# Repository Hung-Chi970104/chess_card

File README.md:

# Pico Chess Card
Ever think of playing chess on the size of a business card? Welcome to the Pico Chess Card!

After building my Tic-Tac-Toe business card, I decided to build a more advanced version that allows users to play chess, compete online through radio, and even compete against AI!

https://github.com/user-attachments/assets/676e2b21-aca0-44f8-8b26-b48a64608b89

# Features
- Pass-and-play mode (like one device but two people take turn)
- Online 1v1 through nrf24l01 (*Will be added in V2!)
- NFC tap to either go to websites or pairing mode

# Components
- RP2040
- 12MHz Crystal (ABM8-272-T3)
- 8MB Flash Storage (W25Q64JVXGIQ)
- Buck-Boost Switching Regulator (RT6150B)
- USB-C (TYPE-C-31-M-12)

# PCB Designs
- 2 layers
- Single-sided component placement
- 2.6mm board thickness
- HASL (with lead) surface finish
- 1oz outer copper weight

## PCB Schematic

## PCB Layouts

## 3D Model

# How to order
- Download the zip file
- Upload the zip file to JLCPCB
- Select PCBA and continue
- Upload BOM.csv and position.csv
- Select the parts and submit payment

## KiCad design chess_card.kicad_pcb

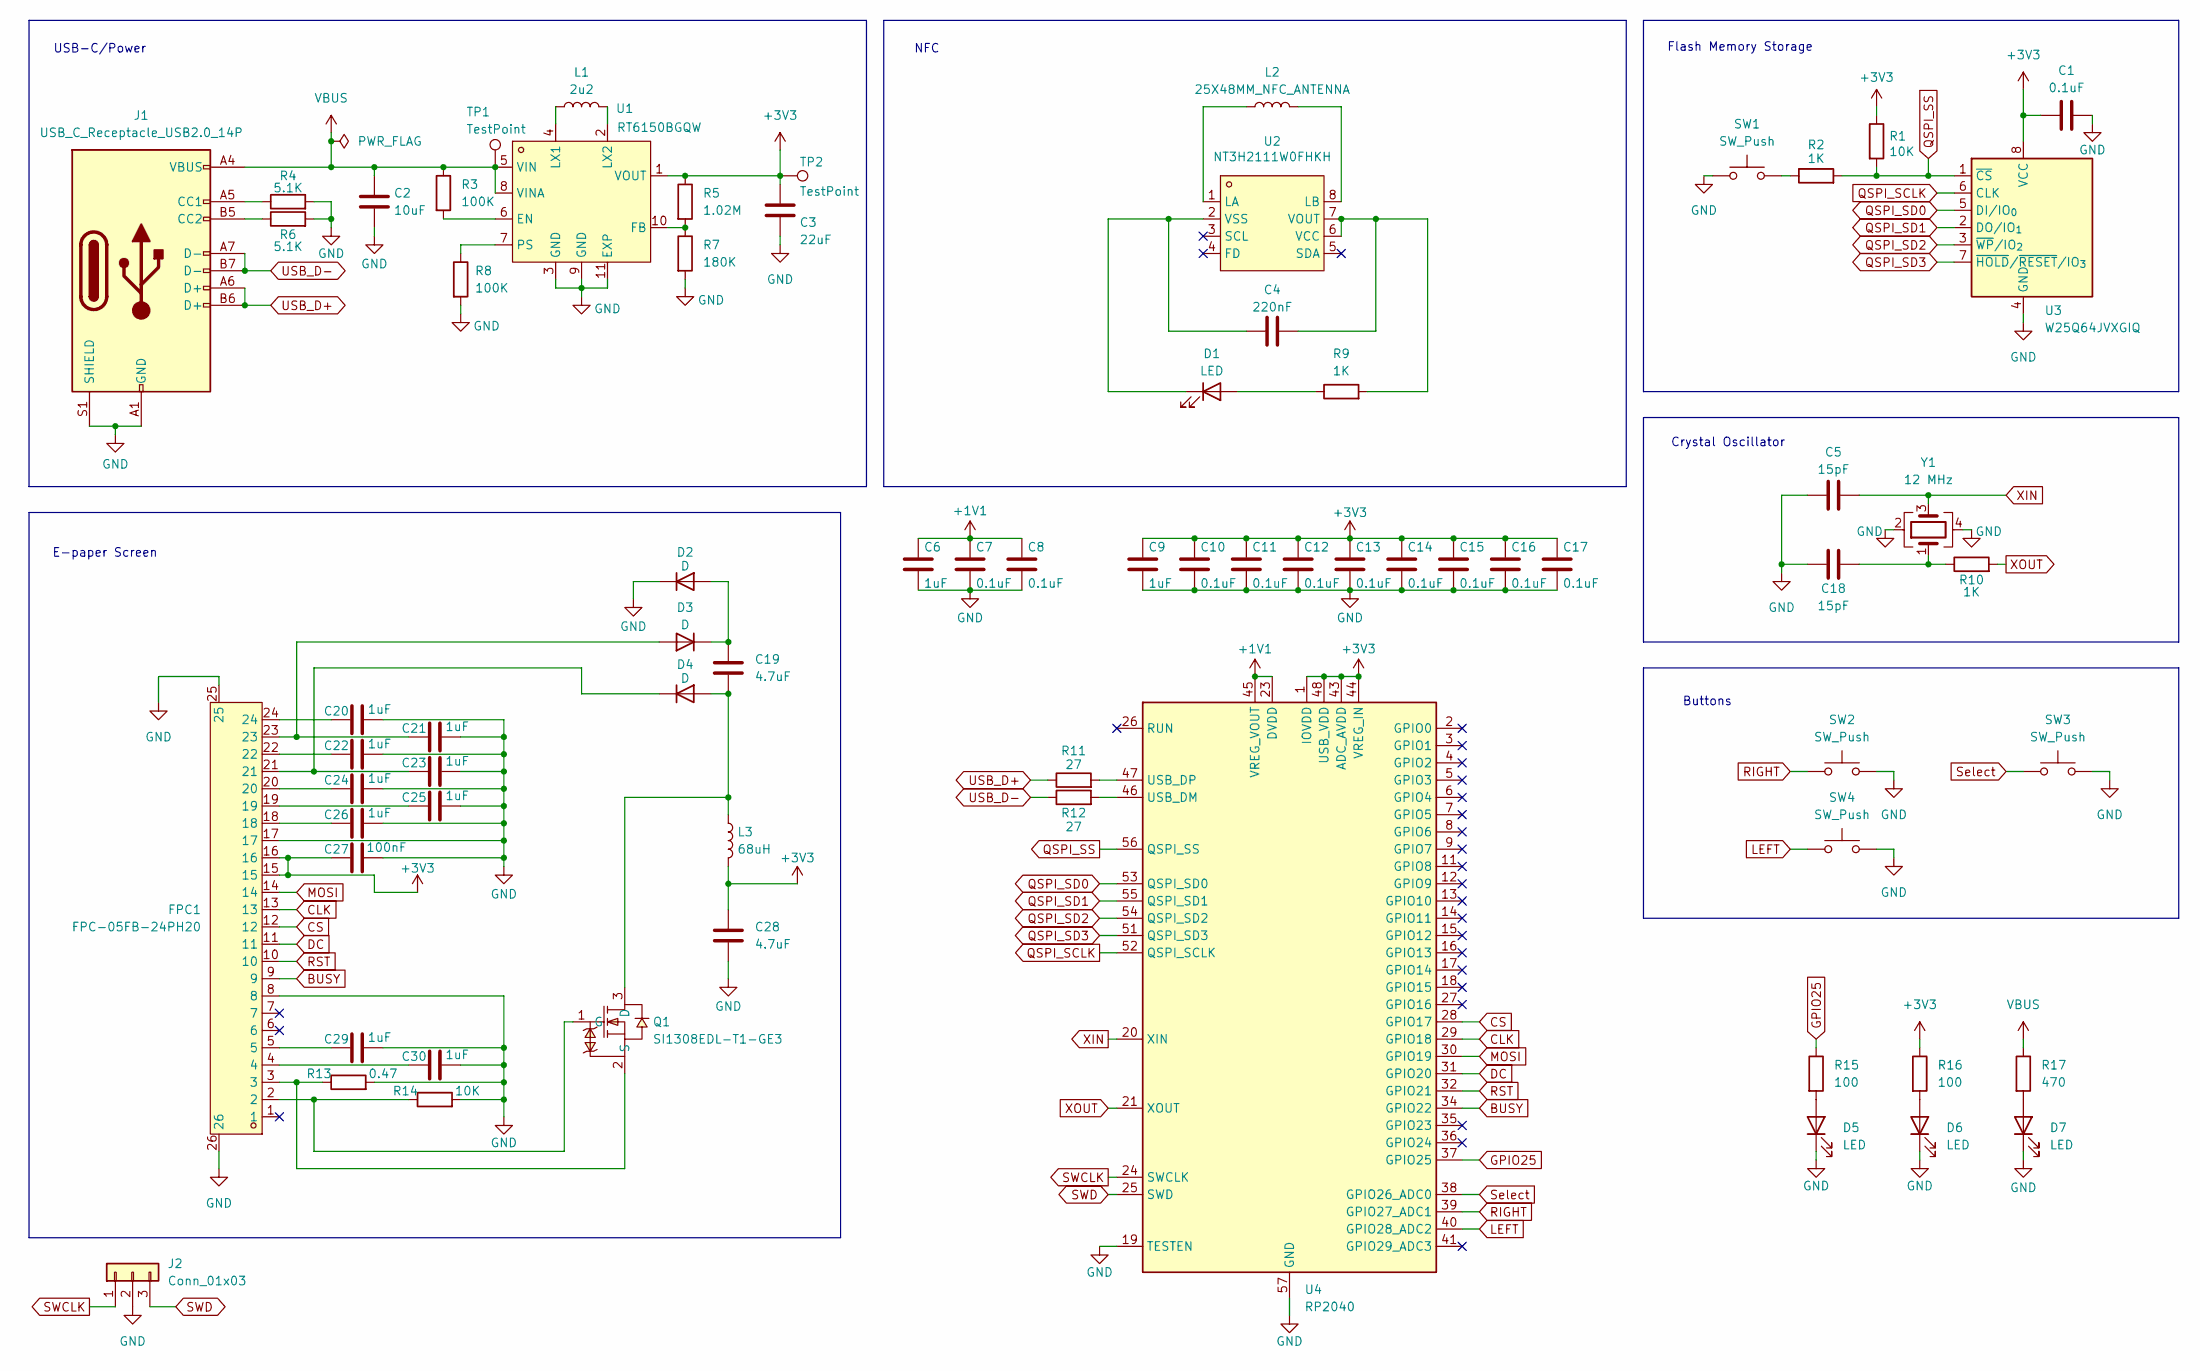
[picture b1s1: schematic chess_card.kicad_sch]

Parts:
C1, C7, C8, C10, C11, C12, C13, C14, C15, C16, C17: 0.1uF; C_0402_1005Metric
C2: 10uF; C_1206_3216Metric
C3: 22uF; C_1206_3216Metric
C4: 220nF; C_0603_1608Metric
C5, C18: 15pF; C_0402_1005Metric
C6, C9: 1uF; C_0402_1005Metric
C19, C28: 4.7uF; C_0603_1608Metric
C20, C21, C22, C23, C24, C25, C26, C29, C30: 1uF; C_0603_1608Metric
C27: 100nF; C_0603_1608Metric
D1: LED; LED_0402_1005Metric
D2, D3, D4: D; D_SOD-323
D5, D6, D7: LED; LED_0805_2012Metric
FPC1: FPC-05FB-24PH20; FPC-SMD_24P-P0.50_FPC-05FB-24PH20; LCSC Part C2856831
J1: USB_C_Receptacle_USB2.0_14P; USB_C_Receptacle_HRO_TYPE-C-31-M-12
J2: Conn_01x03; PinHeader_1x03_P2.54mm_Vertical
L1: 2u2; L_1008_2520Metric
L2: 25X48MM_NFC_ANTENNA
L3: 68uH; L_0805_2012Metric
Q1: SI1308EDL-T1-GE3; SOT-323_L2.0-W1.3-P1.30-LS2.1-BR; LCSC Part C469327
R1: 10K; R_0402_1005Metric
R2, R10: 1K; R_0402_1005Metric
R3, R8: 100K; R_0402_1005Metric
R4, R6: 5.1K; R_0402_1005Metric
R5: 1.02M; R_0402_1005Metric
R7: 180K; R_0402_1005Metric
R9: 1K; R_0402_1005Metric; LCSC C23182
R11, R12: 27; R_0402_1005Metric
R13: 0.47; R_0603_1608Metric
R14: 10K; R_0603_1608Metric
R15, R16: 100; R_0402_1005Metric
R17: 470; R_0402_1005Metric
SW1: SW_Push; SW_Push_SPST_NO_Alps_SKRK
SW2, SW3, SW4: SW_Push; SW_SPST_SKQG_WithoutStem
TP1, TP2: TestPoint; TestPoint_Pad_1.0x1.0mm
U1: RT6150BGQW; WSON-10_L2.5-W2.5-P0.50-BL-EP; LCSC Part C147972
U2: NT3H2111W0FHKH; XQFN-8_L1.6-W1.6-P0.50-BL_NT3H2111W0FHKH; LCSC C710403
U3: W25Q64JVXGIQ; XSON-8_L4.0-W4.0-P0.80-TL-EP
U4: RP2040; QFN-56-1EP_7x7mm_P0.4mm_EP3.2x3.2mm
Y1: 12 MHz; Crystal_SMD_3225-4Pin_3.2x2.5mm

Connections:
+1V1: C6.1, C7.1, C8.1, U4.23 (DVDD), U4.45 (VREG_VOUT), U4.50 (DVDD)
+3V3: C1.1, C3.1, C9.1, C10.1, C11.1, C12.1, C13.1, C14.1, C15.1, C16.1, C17.1, C27.2, C28.1, FPC1.15, FPC1.16, L3.2, R1.1, R5.1, R16.1, TP2.1, U1.1 (VOUT), U3.8 (VCC), U4.1 (IOVDD), U4.10 (IOVDD), U4.22 (IOVDD), U4.33 (IOVDD), U4.42 (IOVDD), U4.43 (ADC_AVDD), U4.44 (VREG_IN), U4.48 (USB_VDD), U4.49 (IOVDD)
BUSY: FPC1.9, U4.34 (GPIO22)
CLK: FPC1.13, U4.29 (GPIO18)
CS: FPC1.12, U4.28 (GPIO17)
DC: FPC1.11, U4.31 (GPIO20)
GND: C1.2, C2.2, C3.2, C5.1, C6.2, C7.2, C8.2, C9.2, C10.2, C11.2, C12.2, C13.2, C14.2, C15.2, C16.2, C17.2, C18.1, C20.1, C21.1, C22.1, C23.1, C24.1, C25.1, C26.1, C27.1, C28.2, C29.1, C30.1, D2.1 (K), D5.1 (K), D6.1 (K), D7.1 (K), FPC1.8, FPC1.17, FPC1.25, FPC1.26, J1.A1 (GND), J1.A12 (GND), J1.B1 (GND), J1.B12 (GND), J1.S1 (SHIELD), J2.2, R4.2, R6.2, R7.2, R8.2, R13.2, R14.2, SW1.1, SW2.2, SW3.2, SW4.2, U1.3 (GND), U1.9 (GND), U1.11 (EXP), U3.4 (GND), U4.19 (TESTEN), U4.57 (GND), Y1.2, Y1.4
GPIO25: R15.1, U4.37 (GPIO25)
LEFT: SW4.1, U4.40 (GPIO28_ADC2)
MOSI: FPC1.14, U4.30 (GPIO19)
unnamed: C18.2, R10.1, Y1.1
unnamed: C20.2, FPC1.24
unnamed: C22.2, FPC1.22
unnamed: C24.2, FPC1.20
unnamed: C25.2, FPC1.19
unnamed: C26.2, FPC1.18
unnamed: C29.2, FPC1.5
unnamed: C30.2, FPC1.4
unnamed: D1.2 (A), R9.1
unnamed: C4.1, D1.1 (K), U2.2 (VSS)
unnamed: C19.1, D2.2 (A), D3.1 (K)
unnamed: C21.2, D3.2 (A), FPC1.23
unnamed: C19.2, D4.2 (A), L3.1, Q1.3 (D)
unnamed: C23.2, D4.1 (K), FPC1.21
unnamed: D5.2 (A), R15.2
unnamed: D6.2 (A), R16.2
unnamed: D7.2 (A), R17.2
unnamed: J1.A5 (CC1), R4.1
unnamed: J1.B5 (CC2), R6.1
unnamed: FPC1.2, Q1.1 (G), R14.1
unnamed: FPC1.3, Q1.2 (S), R13.1
unnamed: R2.1, SW1.2
unnamed: R3.2, U1.6 (EN)
unnamed: R5.2, R7.1, U1.10 (FB)
unnamed: L1.1, U1.4 (LX1)
unnamed: L1.2, U1.2 (LX2)
unnamed: R8.1, U1.7 (PS)
unnamed: L2.1, U2.1 (LA)
unnamed: L2.2, U2.8 (LB)
unnamed: C4.2, R9.2, U2.6 (VCC), U2.7 (VOUT)
unnamed: R12.2, U4.46 (USB_DM)
unnamed: R11.2, U4.47 (USB_DP)
QSPI_SCLK: U3.6 (CLK), U4.52 (QSPI_SCLK)
QSPI_SD0: U3.5 (DI/IO_{0}), U4.53 (QSPI_SD0)
QSPI_SD1: U3.2 (DO/IO_{1}), U4.55 (QSPI_SD1)
QSPI_SD2: U3.3 (~WP/IO_{2}), U4.54 (QSPI_SD2)
QSPI_SD3: U3.7 (~HOLD/~RESET/IO_{3}), U4.51 (QSPI_SD3)
QSPI_SS: R1.2, R2.2, U3.1 (~CS), U4.56 (QSPI_SS)
RIGHT: SW2.1, U4.39 (GPIO27_ADC1)
RST: FPC1.10, U4.32 (GPIO21)
SWCLK: J2.1, U4.24 (SWCLK)
SWD: J2.3, U4.25 (SWD)
Select: SW3.1, U4.38 (GPIO26_ADC0)
USB_D+: J1.A6 (D+), J1.B6 (D+), R11.1
USB_D-: J1.A7 (D-), J1.B7 (D-), R12.1
VBUS: C2.1, J1.A4 (VBUS), J1.A9 (VBUS), J1.B4 (VBUS), J1.B9 (VBUS), R3.1, R17.1, TP1.1, U1.5 (VIN), U1.8 (VINA)
XIN: C5.2, U4.20 (XIN), Y1.3
XOUT: R10.2, U4.21 (XOUT)

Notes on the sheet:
E-paper Screen
Crystal Oscillator
Flash Memory Storage
Buttons
NFC
USB-C/Power

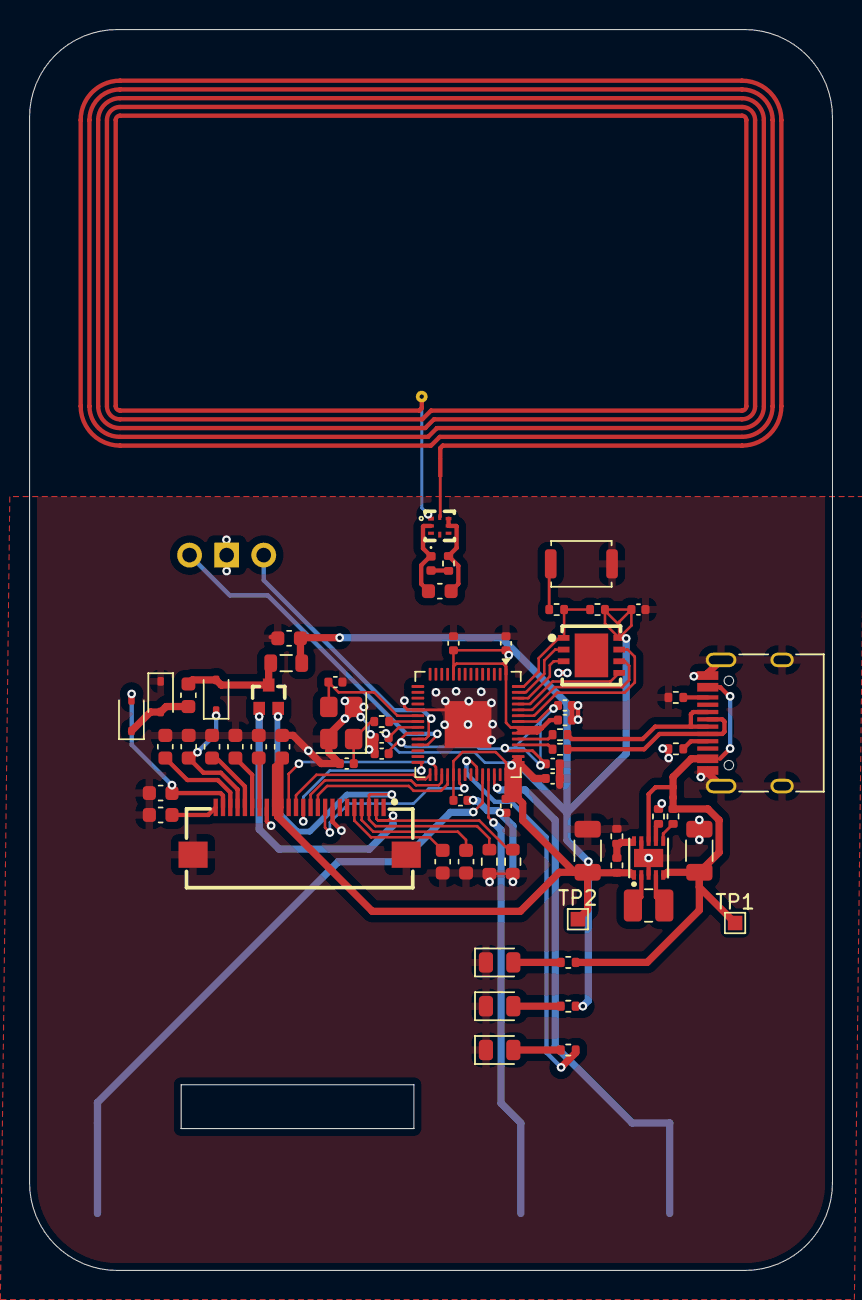
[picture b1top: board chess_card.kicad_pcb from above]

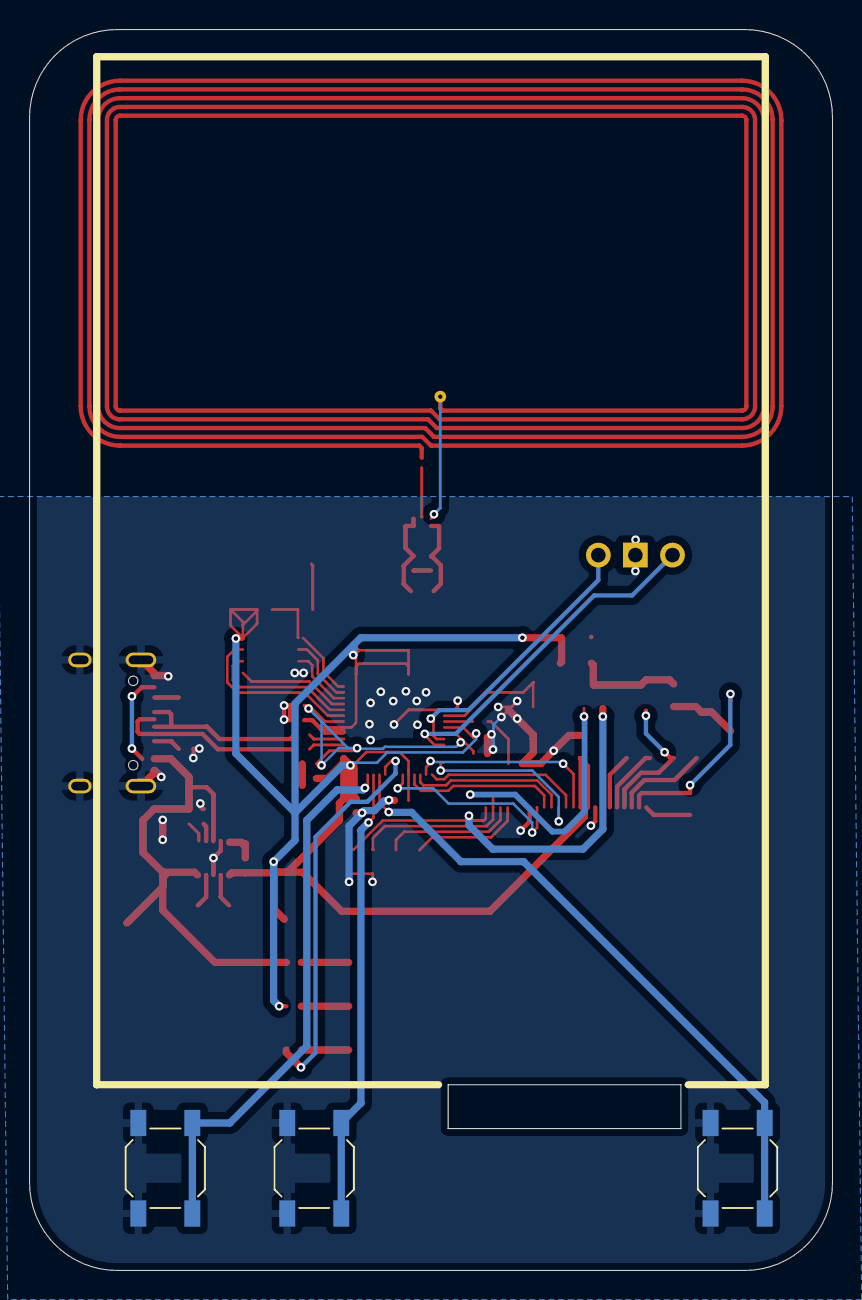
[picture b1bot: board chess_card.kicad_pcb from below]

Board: 2 copper layers, 55.0 x 85.0 mm, 70 parts (3 on the bottom side), 58 nets.

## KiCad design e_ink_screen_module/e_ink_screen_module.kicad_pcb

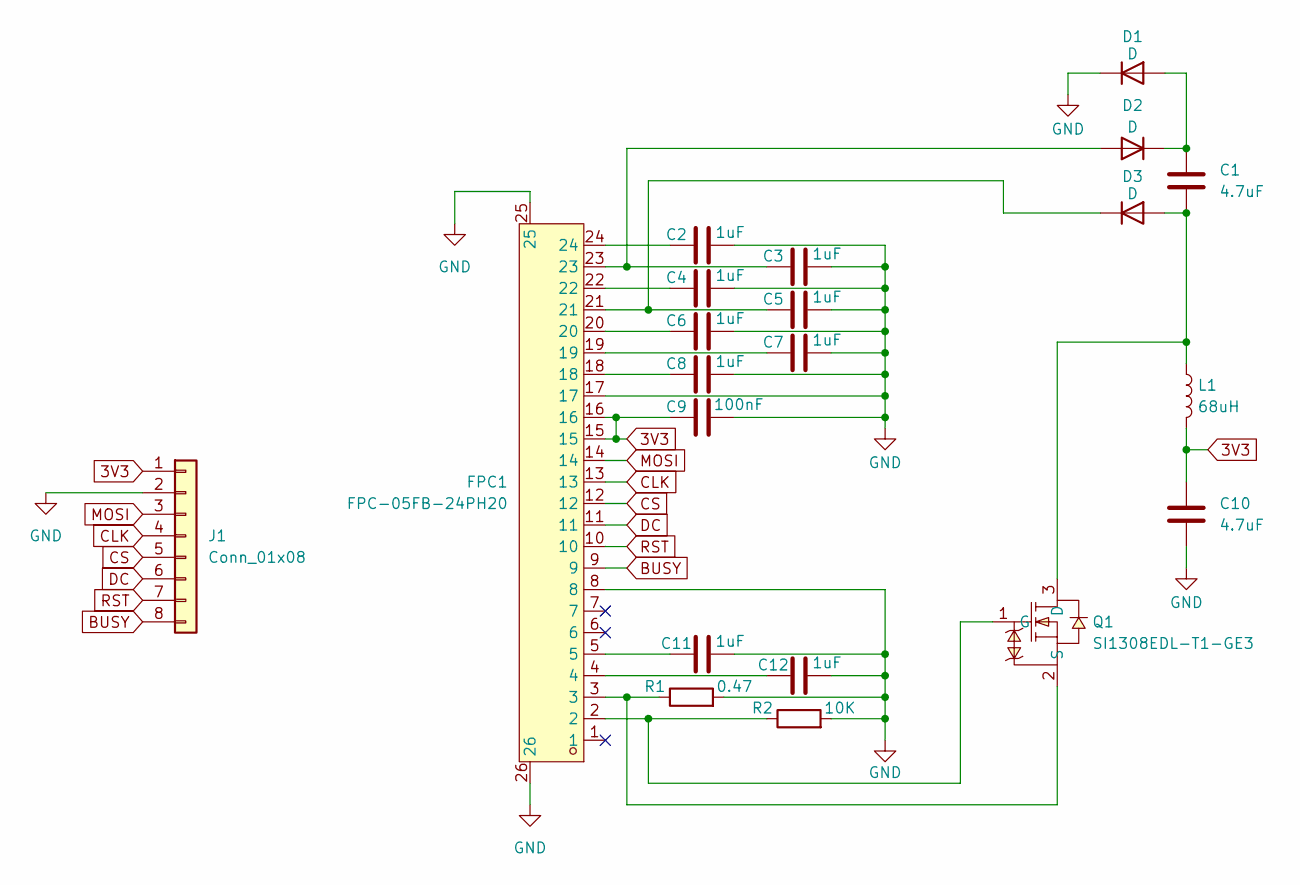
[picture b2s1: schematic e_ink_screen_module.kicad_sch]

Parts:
C1, C10: 4.7uF; C_0603_1608Metric
C2, C3, C4, C5, C6, C7, C8, C11, C12: 1uF; C_0603_1608Metric
C9: 100nF; C_0603_1608Metric
D1, D2, D3: D; D_SOD-323
FPC1: FPC-05FB-24PH20; FPC-SMD_24P-P0.50_FPC-05FB-24PH20; LCSC Part C2856831
J1: Conn_01x08; PinHeader_1x08_P2.54mm_Vertical
L1: 68uH; L_0805_2012Metric
Q1: SI1308EDL-T1-GE3; SOT-323_L2.0-W1.3-P1.30-LS2.1-BR; LCSC Part C469327
R1: 0.47; R_0603_1608Metric
R2: 10K; R_0603_1608Metric

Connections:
3V3: C9.2, C10.1, FPC1.15, FPC1.16, J1.1, L1.2
BUSY: FPC1.9, J1.8
CLK: FPC1.13, J1.4
CS: FPC1.12, J1.5
DC: FPC1.11, J1.6
GND: C2.1, C3.1, C4.1, C5.1, C6.1, C7.1, C8.1, C9.1, C10.2, C11.1, C12.1, D1.1 (K), FPC1.8, FPC1.17, FPC1.25, FPC1.26, J1.2, R1.2, R2.2
MOSI: FPC1.14, J1.3
unnamed: C2.2, FPC1.24
unnamed: C4.2, FPC1.22
unnamed: C6.2, FPC1.20
unnamed: C7.2, FPC1.19
unnamed: C8.2, FPC1.18
unnamed: C11.2, FPC1.5
unnamed: C12.2, FPC1.4
unnamed: C1.1, D1.2 (A), D2.1 (K)
unnamed: C3.2, D2.2 (A), FPC1.23
unnamed: C1.2, D3.2 (A), L1.1, Q1.3 (D)
unnamed: C5.2, D3.1 (K), FPC1.21
unnamed: FPC1.2, Q1.1 (G), R2.1
unnamed: FPC1.3, Q1.2 (S), R1.1
RST: FPC1.10, J1.7

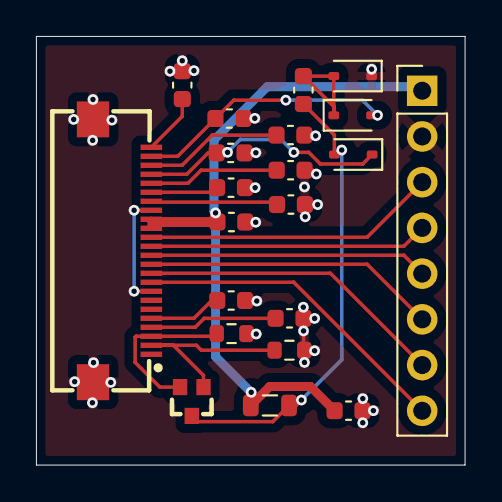
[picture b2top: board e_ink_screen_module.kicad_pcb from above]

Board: 2 copper layers, 23.8 x 23.8 mm, 21 parts (0 on the bottom side), 21 nets.

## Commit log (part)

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2026-04-27 Add project assets link to README
    Added a link to the project assets in the README.
